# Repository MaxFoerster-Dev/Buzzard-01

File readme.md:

# Buzzard-01

## The Rocket

### How I came up with the idea:

I watched a couple of [BPS.space](https://www.youtube.com/bpsspace) YouTube videos and thought _it's not gonna be that hard..._  
I remembered a c't magazine article about the program **OpenRocket** and I tried it. My final rocket was this:

### Why a Flight Computer?

Although it sounds like overkill, to put a flight computer on to the first ever build rocket, I did it.  
Since I was familiar with **KiCad** I choose to design the flight computer with KiCad.  
I came up with this design, featuring up to 3 sensors (MPU-6050-A, SGP40 and an BMP280), a XIAO-ESP32-S3 module and a place for the battery and an ON/OFF switch:

### Future Plans / Software

The next step is writing the flight software. I will probably use **MicroPython** to read the sensor data and control the rocket.

## Use of the Files

### .ork files (OpenRocket)

Open these files with **OpenRocket** to view or modify the rocket design and simulations.

- **How to open:** In OpenRocket, press `Ctrl+O` (or `Cmd+O` on Mac), navigate to the file, and open it.

### .kicad_pcb / .kicad_sch files (KiCad)

These files contain the schematics and PCB layout for the custom flight computer.

- **How to open:** Open **KiCad**, select `File` > `Open Project`, and select the project file in this directory.

### 3D Models (.obj / .stl)

These files contain the 3D-printable components of the rocket (like the nose cone or fins) and 3D renders of the electronics.

- **How to use:** Import the `.obj` files directly into your preferred 3D printing slicer (e.g., Cura, PrusaSlicer) or a CAD program (e.g., Blender, FreeCAD) for modifications.

### 🛠️ Required Software & Toolchain

To view, modify, or build this project, you will need the following software:

| Software | Purpose / Usage | Recommended Version |
| :--- | :--- | :--- |
| **[OpenRocket](https://openrocket.info)** | Rocket flight simulation and design (`.ork` files) | v23.09 or newer |
| **[KiCad](https://kicad.org)** | PCB Design & Schematics (`.kicad_*` files) | v8.x or newer |
| **[MicroPython](https://micropython.org)** | Flight controller firmware (ESP32) | v1.22+ |
| **[Thonny](https://thonny.org)** or **[VS Code](https://code.visualstudio.com/download)** | Recommended IDE for flashing and writing MicroPython | Latest |
| **Any 3D Slicer** (e.g., [Cura](https://curaslicer.com/), [PrusaSlicer](https://www.prusa3d.com/p/prusaslicer/)) | Slicing `.stl`/`.obj` files for 3D printing | - |

## Security & Safety

Building and launching model rockets involves inherent physical and electrical risks. Please read the [Security Policy](https://github.com/MaxFoerster-Dev/Buzzard-01/security/policy) for important safety disclaimers, launch regulations, and instructions on how to report critical hardware or software flaws.

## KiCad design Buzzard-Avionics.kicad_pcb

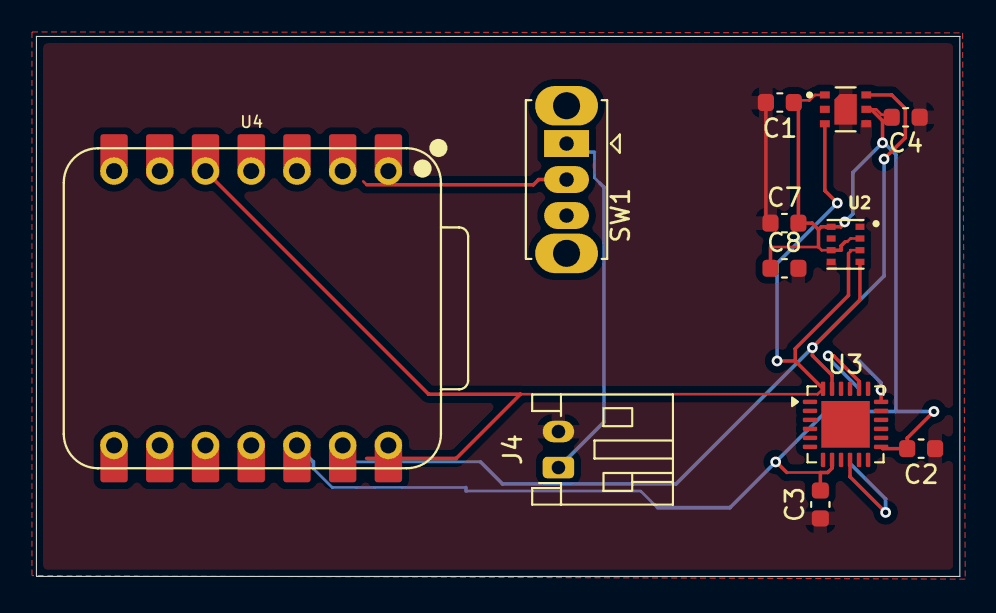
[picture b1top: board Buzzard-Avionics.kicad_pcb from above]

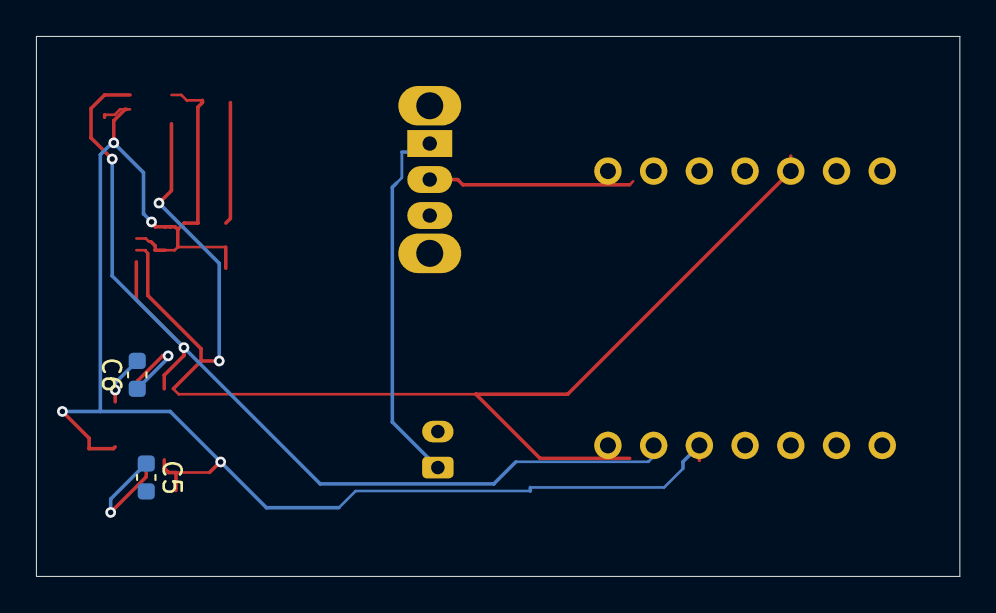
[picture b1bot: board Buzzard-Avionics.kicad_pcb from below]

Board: 2 copper layers, 51.3 x 30.0 mm, 14 parts (2 on the bottom side), 7 nets.

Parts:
C1: 1uF; C_0603_1608Metric
C2, C3, C4, C5, C7: 100nF; C_0603_1608Metric
C6: 2,2nF; C_0603_1608Metric
C8: 10nF; C_0603_1608Metric
J4: Conn_01x02_Socket; JST_PH_S2B-PH-K_1x02_P2.00mm_Horizontal
SW1: SW_SPDT; SW_Slide_SPDT_Straight_CK_OS102011MS2Q
U1: SGP40; XCDR_SGP40-D-R4
U2: BMP280; XDCR_BMP280
U3: MPU-6050-A; QFN-24-1EP_4x4mm_P0.5mm_EP2.7x2.6mm
U4: XIAO-ESP32-S3-SMD; XIAO-ESP32-S3-DIP

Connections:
/+3V3: C1.1, C2.2, C3.2, C4.2, C7.2, C8.1, U1.1 (VDD), U1.5 (VDDH), U2.2 (CSB), U2.6 (VDDIO), U2.8 (VDD), U3.8 (VLOGIC), U3.13 (VDD), U4.12 (3V3_OUT)
/I2C_SCL: U1.6 (SCL), U2.4 (SCK), U3.23 (SCL), U4.6 (D5)
/I2C_SDA: U1.3 (SDA), U2.3 (SDI), U3.24 (SDA), U4.5 (D4)
/V_BATT: J4.1, SW1.1 (A)
GND: C1.2, C2.1, C3.1, C4.1, C5.2, C6.2, C7.1, C8.2, J4.2, U1.2 (VSS), U1.4 (N/A), U1.7 (EXP), U2.1 (GND), U2.5 (SDO), U2.7 (GND), U3.1 (CLKIN), U3.9 (AD0), U3.11 (FSYNC), U3.18 (GND)
unnamed: C6.1, U3.20 (CPOUT)
unnamed: C5.1, U3.10 (REGOUT)

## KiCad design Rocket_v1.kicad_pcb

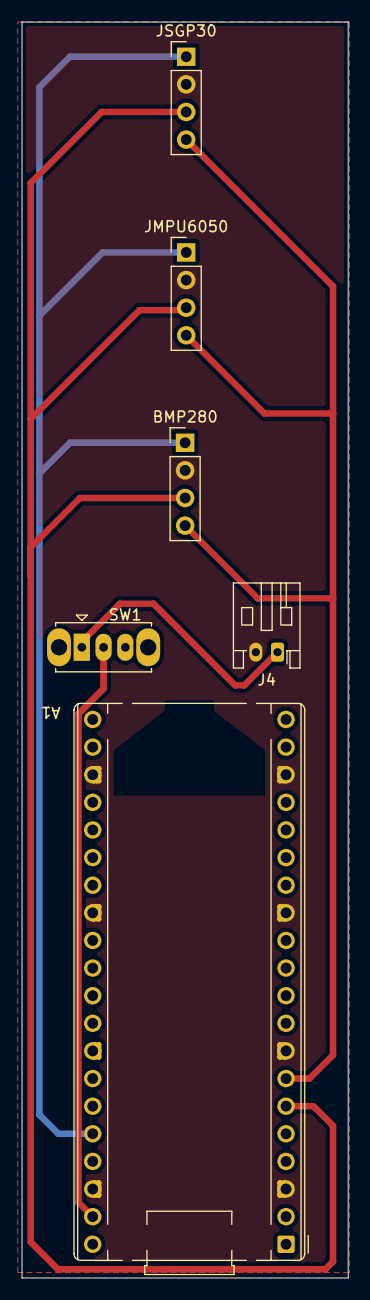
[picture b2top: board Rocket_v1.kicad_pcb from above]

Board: 2 copper layers, 30.0 x 115.5 mm, 6 parts (0 on the bottom side), 6 nets.

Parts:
A1: RaspberryPi_Pico; RaspberryPi_Pico_Common_THT
BMP280: Conn_01x04_Pin; PinHeader_1x04_P2.54mm_Vertical
J4: Conn_01x02_Socket; JST_PH_S2B-PH-K_1x02_P2.00mm_Horizontal
JMPU6050: Conn_01x04_Pin; PinHeader_1x04_P2.54mm_Vertical
JSGP30: Conn_01x04_Pin; PinHeader_1x04_P2.54mm_Vertical
SW1: SW_SPDT; SW_Slide_SPDT_Straight_CK_OS102011MS2Q

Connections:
/+3V3: A1.36 (3V3), BMP280.1, JMPU6050.1, JSGP30.1
/GND: A1.3 (GND), A1.8 (GND), A1.13 (GND), A1.18 (GND), A1.23 (GND), A1.28 (GND), A1.38 (GND), BMP280.2, J4.2, JMPU6050.2, JSGP30.2
/I2C_SCL: A1.6 (GPIO4), BMP280.3, JMPU6050.3, JSGP30.3
/I2C_SDA: A1.7 (GPIO5), BMP280.4, JMPU6050.4, JSGP30.4
/V_BATT: J4.1, SW1.1 (A)
unnamed: A1.39 (VSYS), SW1.2 (B)

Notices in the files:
readme.md:
License: CC BY-NC-SA 4.0
